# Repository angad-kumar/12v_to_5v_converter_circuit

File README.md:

# 3D Image

# Schematics 

# Layout

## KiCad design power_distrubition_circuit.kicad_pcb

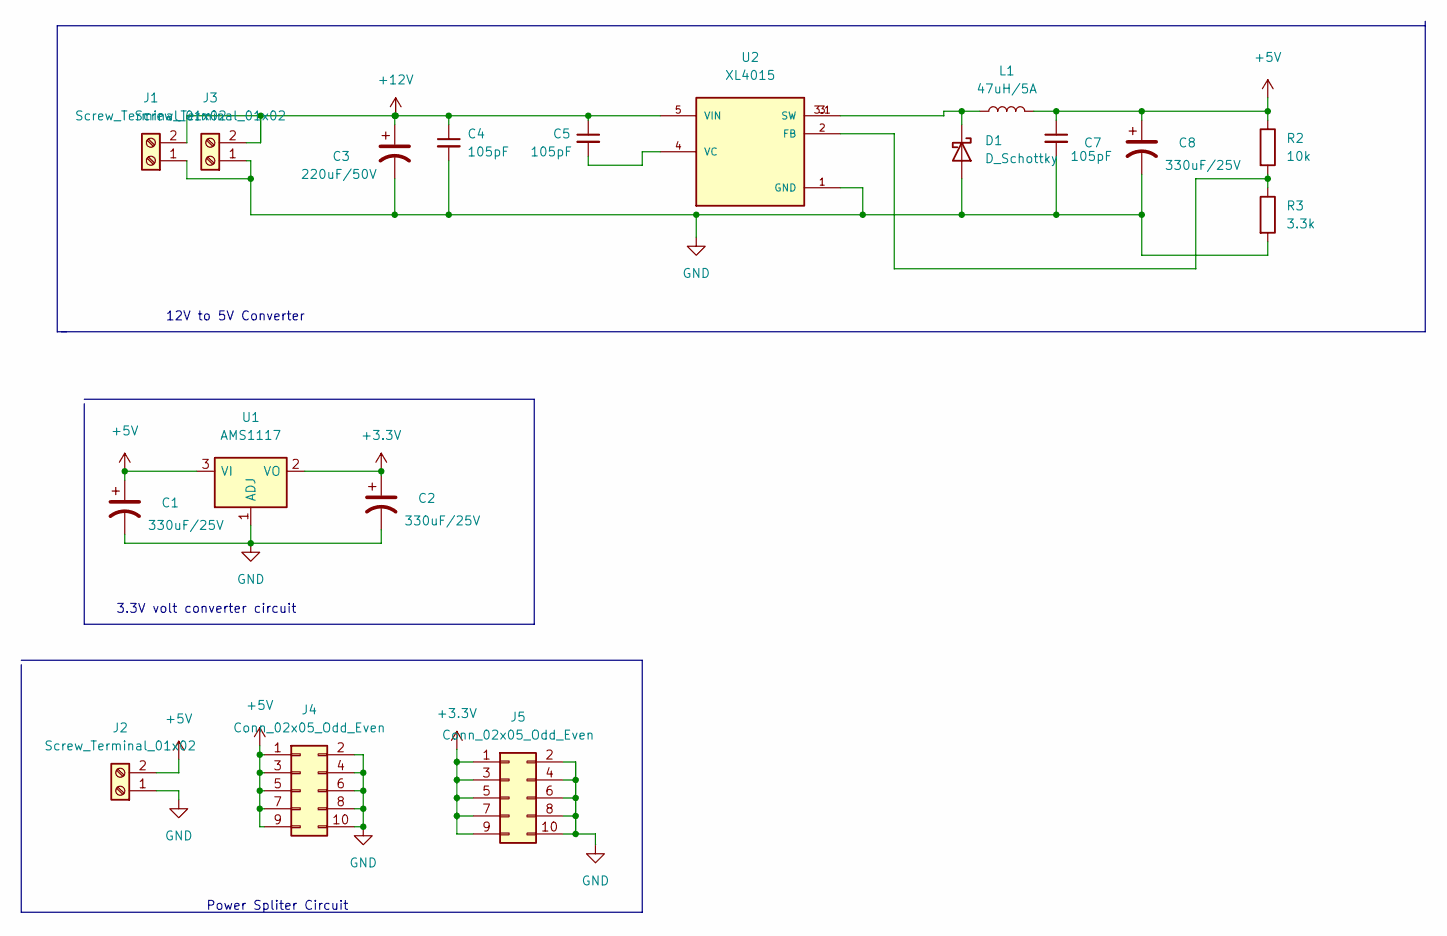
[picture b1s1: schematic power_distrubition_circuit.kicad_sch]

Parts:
C1, C2, C8: 330uF/25V; CP_Elec_10x10.5
C3: 220uF/50V; CP_Elec_8x10.5
C4, C5, C7: 105pF; C_0805_2012Metric
D1: D_Schottky; D_SMA
J1: Screw_Terminal_01x02; AMASS_XT60-F_1x02_P7.20mm_Vertical
J2, J3: Screw_Terminal_01x02; TerminalBlock_bornier-2_P5.08mm
J4, J5: Conn_02x05_Odd_Even; PinSocket_2x05_P2.54mm_Vertical
L1: 47uH/5A; L_Toroid_Vertical_L21.6mm_W8.4mm_P8.38mm_Pulse_G
R2: 10k; R_0805_2012Metric
R3: 3.3k; R_0805_2012Metric
U1: AMS1117; SOT-223-3_TabPin2
U2: XL4015; CONV_XL4015; PARTREV 1.5

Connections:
+3.3V: C2.1, J5.1, J5.3, J5.5, J5.7, J5.9, U1.2 (VO)
+5V: C1.1, C7.1, C8.1, J2.2, J4.1, J4.3, J4.5, J4.7, J4.9, L1.2, R2.1, U1.3 (VI)
+12V: C3.1, C4.1, C5.1, J1.2, J3.2, U2.5 (VIN)
GND: C1.2, C2.2, C3.2, C4.2, C7.2, C8.2, D1.2 (A), J1.1, J2.1, J3.1, J4.2, J4.4, J4.6, J4.8, J4.10, J5.2, J5.4, J5.6, J5.8, J5.10, R3.2, U1.1 (ADJ), U2.1 (GND)
unnamed: C5.2, U2.4 (VC)
unnamed: D1.1 (K), L1.1, U2.3 (SW), U2.3.1 (SW)
unnamed: R2.2, R3.1, U2.2 (FB)

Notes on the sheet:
3.3V volt converter circuit
12V to 5V Converter
Power Spliter Circuit

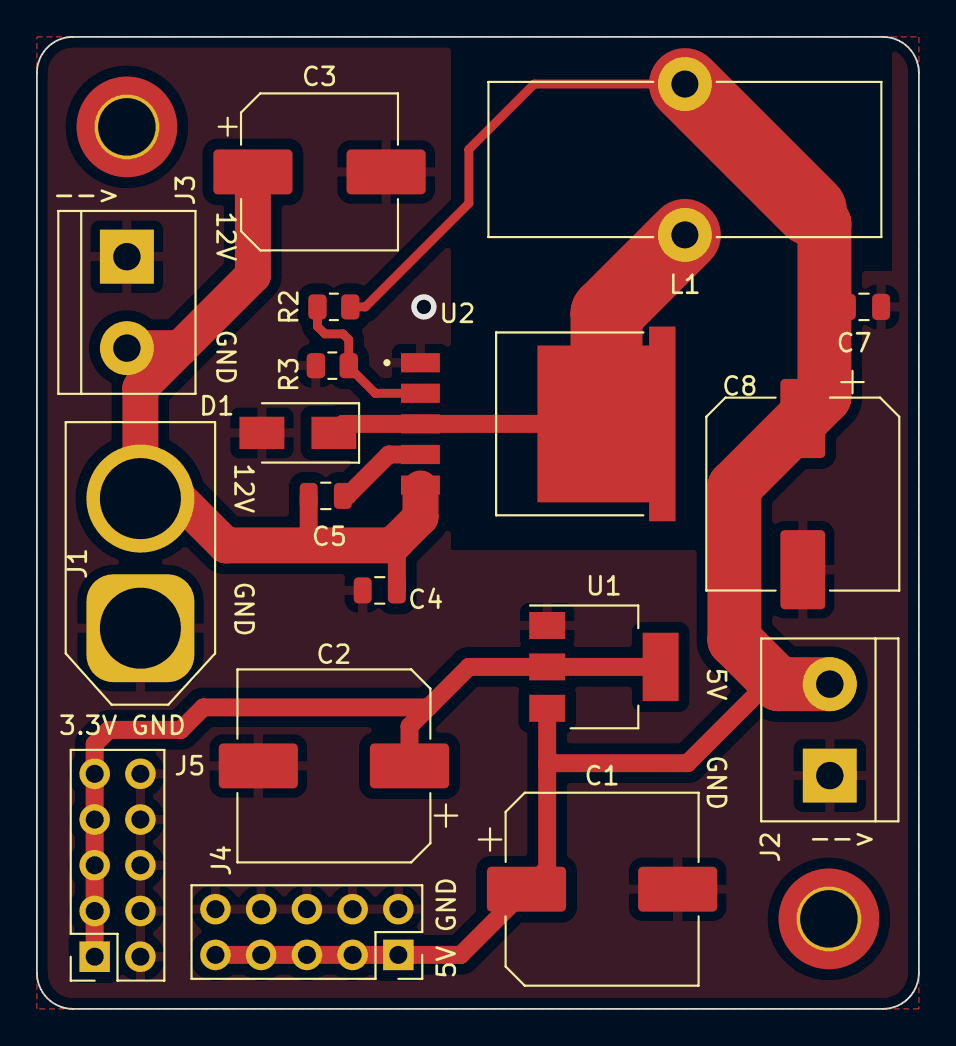
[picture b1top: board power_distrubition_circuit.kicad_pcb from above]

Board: 2 copper layers, 49.0 x 54.0 mm, 18 parts (0 on the bottom side), 7 nets.
